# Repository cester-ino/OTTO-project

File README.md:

## OTTO-project
Hardware prototype for the OTTO Synthesizer 

Use Kicad to open the project

The main features are (for now):

 - **50 key button matrix** 
 - **4 clickable color coded encoders**
 - **1W Audio amplifier** for the internal speaker
 - **Battery management and charging** circuit for the lipo/li-ion batteries and a led battery meter  
 - **Gpio breakout** to allow to position the Raspberry rotated 90 degrees to access the USB ports and to easely use both the LCD screen and the audio card.

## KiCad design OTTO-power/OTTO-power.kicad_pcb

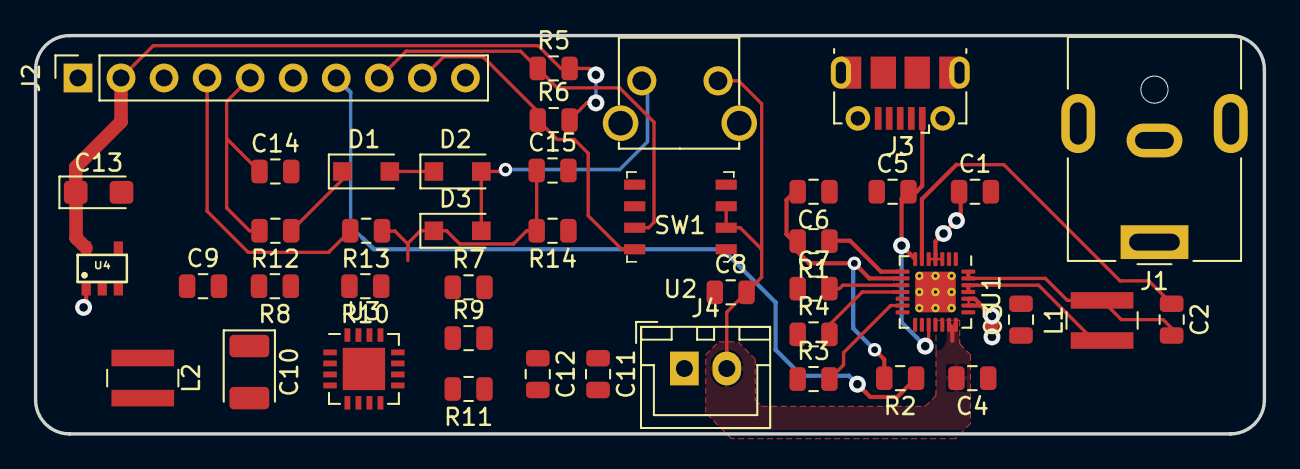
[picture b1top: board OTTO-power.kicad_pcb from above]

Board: 2 copper layers, 72.5 x 23.5 mm, 43 parts (0 on the bottom side), 27 nets.

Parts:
C1, C6, C9: 2.2uf; C_0805_2012Metric
C2: 1uf; C_0805_2012Metric
C3, C4, C11: 10uf; C_0805_2012Metric
C5: 4.7uf; C_0805_2012Metric
C7: 0.15uf; C_0805_2012Metric
C8, C12: 0.1uf; C_0805_2012Metric
C10: 100uf; CP_EIA-3528-21_Kemet-B
C13: 10uf; CP_EIA-3216-18_Kemet-A
C14, C15: 0.1uF; C_0805_2012Metric
D1, D2, D3: IN4001; D_SOD-123F
J1: Barrel_Jack; BarrelJack_CUI_PJ-063AH_Horizontal
J2: Conn_01x10; PinSocket_1x10_P2.54mm_Vertical
J3: USB_B_Micro; USB_Micro-B_Molex-105017-0001
J4: battery; JST_XH_B02B-XH-A_1x02_P2.50mm_Vertical
L1: 3.3uH; L_Wuerth_MAPI-4020
L2: 6.8uH; L_Wuerth_MAPI-4020
R1, R2, R5, R6: 100K; R_0805_2012Metric
R3: 1.2K; R_0805_2012Metric
R4: 3K; R_0805_2012Metric
R7, R10: 200K; R_0805_2012Metric
R8, R9: 1.87M; R_0805_2012Metric
R11: 340K; R_0805_2012Metric
R12, R13, R14: 10K; R_0805_2012Metric
SW1: SW_Push; SKHHLVA010
U1: MAX8903A; QFN-28-1EP_4x4mm_P0.4mm_EP2.4x2.4mm_ThermalVias
U2: MAX17048; TDFN-8-1EP
U3: TPS61090; QFN-16-1EP_4x4mm_P0.65mm_EP2.5x2.5mm
U4: XC6210; SOT25

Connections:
3V3: C13.1, J2.2, R5.2, R6.2, U4.5
5V: C9.2, C10.1, J2.3, R8.2, U3.1, U3.15, U3.16
BATT+: C4.2, C8.2, J4.2, R7.2, SW1.1, U1.20, U1.21, U2.2, U2.3
CHG_OUT: J2.7, R2.1, U1.22
DC: C1.1, J1.1, U1.3, U1.4, U1.5
DOK_OUT: J2.6, R1.1, U1.8
EN_PI: C15.1, D3.1, R7.1, R13.1, R14.2, U3.11, U4.3
GNDA: C1.2, C3.1, C4.1, C5.1, C6.1, C7.1, C8.1, C9.1, C10.2, C11.1, C12.1, C13.2, C14.2, C15.2, J1.2, J2.1, J2.10, J3.5, J4.1, R3.1, R4.1, R10.1, R11.1, R14.1, U1.1, U1.2, U1.12, U1.14, U1.15, U1.16, U2.1, U2.4, U2.6, U3.5, U3.6, U3.7, U3.10, U3.13, U3.17, U4.2
unnamed: C2.1, U1.6
unnamed: C2.2, L1.2, U1.27, U1.28
unnamed: C7.2, U1.10
unnamed: D1.1, R12.1
unnamed: D1.2, D2.1
unnamed: D2.2, D3.2, SW1.2
unnamed: L1.1, U1.25, U1.26
unnamed: L2.1, U3.3, U3.4
unnamed: R3.2, U1.13
unnamed: R4.2, U1.11
unnamed: R8.1, R10.2, U3.14
unnamed: R9.1, R11.2, U3.9
OUT_PIN: J2.4, R13.2
SCL: J2.8, R5.1, U2.7
SDA: J2.9, R6.1, U2.8
SENSE_PIN: C14.1, J2.5, R12.2
SYS: C3.2, C11.2, C12.2, L2.2, R9.2, U1.23, U1.24, U3.8, U4.1
USB: C5.2, J3.1, U1.7, U1.17
VL: C6.2, R1.2, R2.2, U1.9

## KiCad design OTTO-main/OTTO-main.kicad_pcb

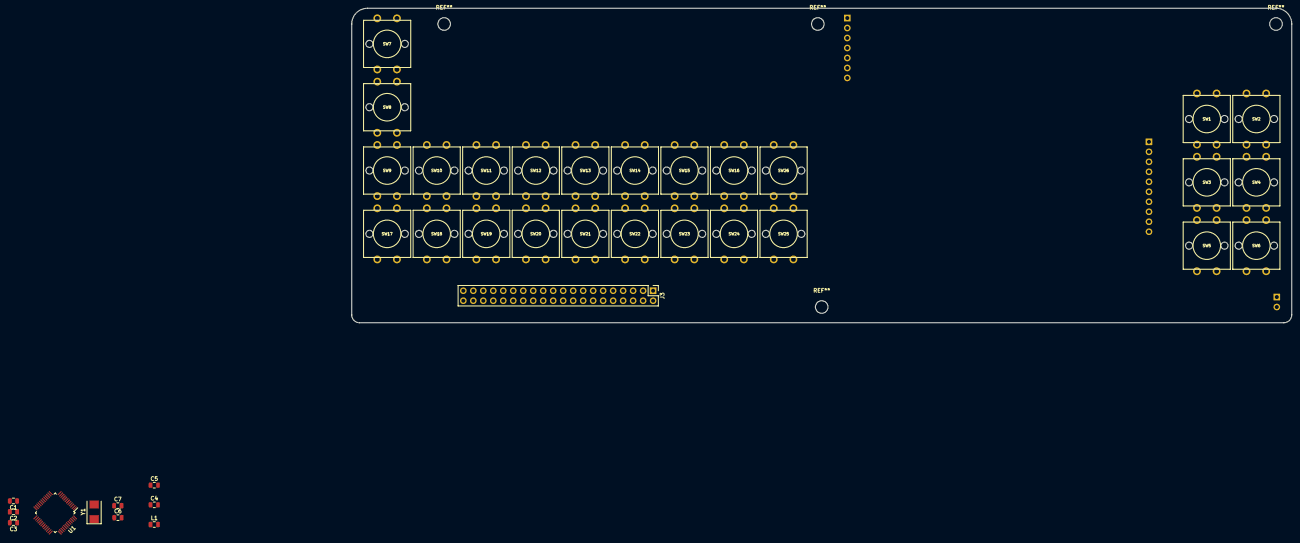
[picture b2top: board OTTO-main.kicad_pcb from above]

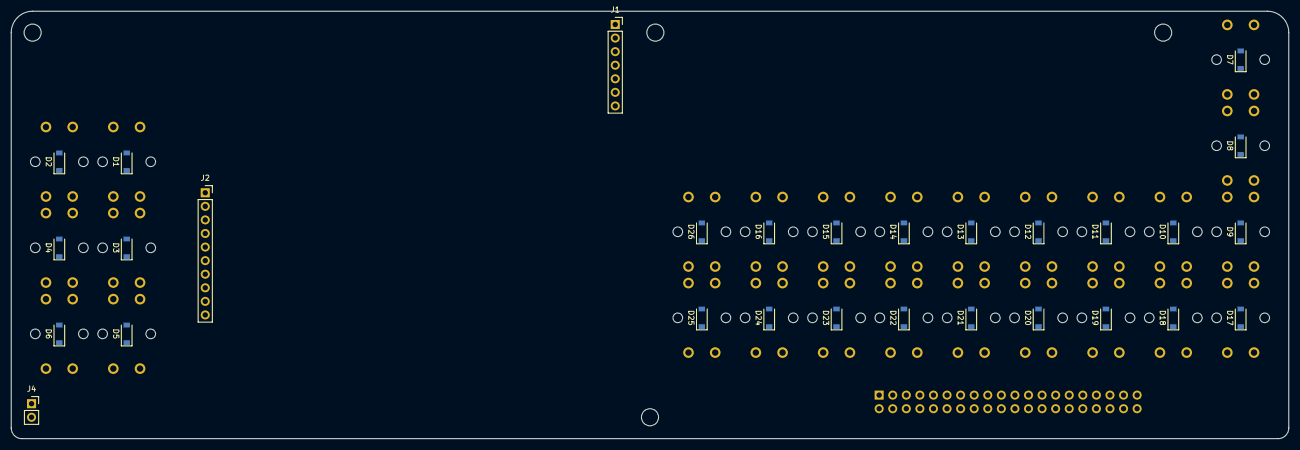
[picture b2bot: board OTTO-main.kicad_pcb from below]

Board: 2 copper layers, 239.0 x 80.0 mm, 66 parts (29 on the bottom side), 57 nets, no tracks yet.

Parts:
C1, C2, C3, C4: 1uf; C_0805_2012Metric
C5: 10nf; C_0805_2012Metric
C6, C7: 22pf; C_0805_2012Metric
D1, D2, D3, D4, D5, D6, D7, D8, D9, D10, D11, D12, D13, D14, D15, D16, D17, D18, D19, D20, D21, D22, D23, D24, D25, D26: D_ALT; D_SOD-123
J1: POWER_BOARD; PinSocket_1x07_P2.54mm_Vertical
J2: AUDIO_BOARD; PinSocket_1x10_P2.54mm_Vertical
J3: Raspberry_Pi_2_3; PinHeader_2x20_P2.54mm_Vertical
J4: MICROPHONE; PinSocket_1x02_P2.54mm_Vertical
L1: 30ohm; C_0805_2012Metric
SW1, SW2, SW3, SW4, SW5, SW6, SW7, SW8, SW9, SW10, SW11, SW12, SW13, SW14, SW15, SW16, SW17, SW18, SW19, SW20, SW21, SW22, SW23, SW24, SW25, SW26: SW_SPST; Tactile_Switch_12x12x7.3_mm
U1: STM32F103CBTx; LQFP-48_7x7mm_P0.5mm
Y1: 8mhz; Crystal_SMD_5032-2Pin_5.0x3.2mm

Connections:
5V: J1.2, J2.8
+3V3: C1.1, C2.1, C3.1, L1.2, U1.24, U1.36, U1.48
BCLK: J2.3, J3.12
COL1: D1.1, D7.1, D17.1
COL2: D2.1, D8.1, D18.1
COL3: D9.1, D19.1
COL4: D10.1, D20.1
COL5: D11.1, D21.1
COL6: D12.1, D22.1
COL7: D3.1, D13.1, D23.1
COL8: D4.1, D14.1, D24.1
COL9: D5.1, D15.1, D25.1
COL10: D6.1, D16.1, D26.1
GNDREF: C1.2, C2.2, C3.2, C4.2, C5.2, C6.2, C7.2, J2.1, J2.9, J3.6, J3.9, J3.14, J3.20, J3.25, J3.30, J3.34, J3.39, U1.44
I2S_RX: J2.4, J3.40
I2S_TX: J2.5, J3.38
LED_G: J1.6, J3.18
LED_R: J1.7, J3.22
LR_CLK: J2.2, J3.35
unnamed: C4.1, C5.1, L1.1, U1.9
unnamed: D1.2, SW1.2
unnamed: D2.2, SW2.2
unnamed: D3.2, SW3.2
unnamed: D4.2, SW4.2
unnamed: D5.2, SW5.2
unnamed: D6.2, SW6.2
unnamed: D7.2, SW7.2
unnamed: D8.2, SW8.2
unnamed: D9.2, SW9.2
unnamed: D10.2, SW10.2
unnamed: D11.2, SW11.2
unnamed: D12.2, SW12.2
unnamed: D13.2, SW13.2
unnamed: D14.2, SW14.2
unnamed: D15.2, SW15.2
unnamed: D16.2, SW16.2
unnamed: D17.2, SW17.2
unnamed: D18.2, SW18.2
unnamed: D19.2, SW19.2
unnamed: D20.2, SW20.2
unnamed: D21.2, SW21.2
unnamed: D22.2, SW22.2
unnamed: D23.2, SW23.2
unnamed: D24.2, SW24.2
unnamed: D25.2, SW25.2
unnamed: D26.2, SW26.2
OSC_IN: C6.1, U1.5, Y1.1
OSC_OUT: C7.1, U1.6, Y1.2
OUT_PIN: J1.4, J3.15
ROW1: SW1.1, SW2.1, SW3.1, SW4.1, SW5.1, SW6.1
ROW2: SW7.1, SW8.1, SW9.1, SW10.1, SW11.1, SW12.1, SW13.1, SW14.1, SW15.1, SW16.1
ROW3: SW17.1, SW18.1, SW19.1, SW20.1, SW21.1, SW22.1, SW23.1, SW24.1, SW25.1, SW26.1
SCL: J2.7, J3.5
SDA: J2.6, J3.3
SENSE_PIN: J1.5, J3.16
UART_RXD: J3.10, U1.30
UART_TXD: J3.8, U1.31

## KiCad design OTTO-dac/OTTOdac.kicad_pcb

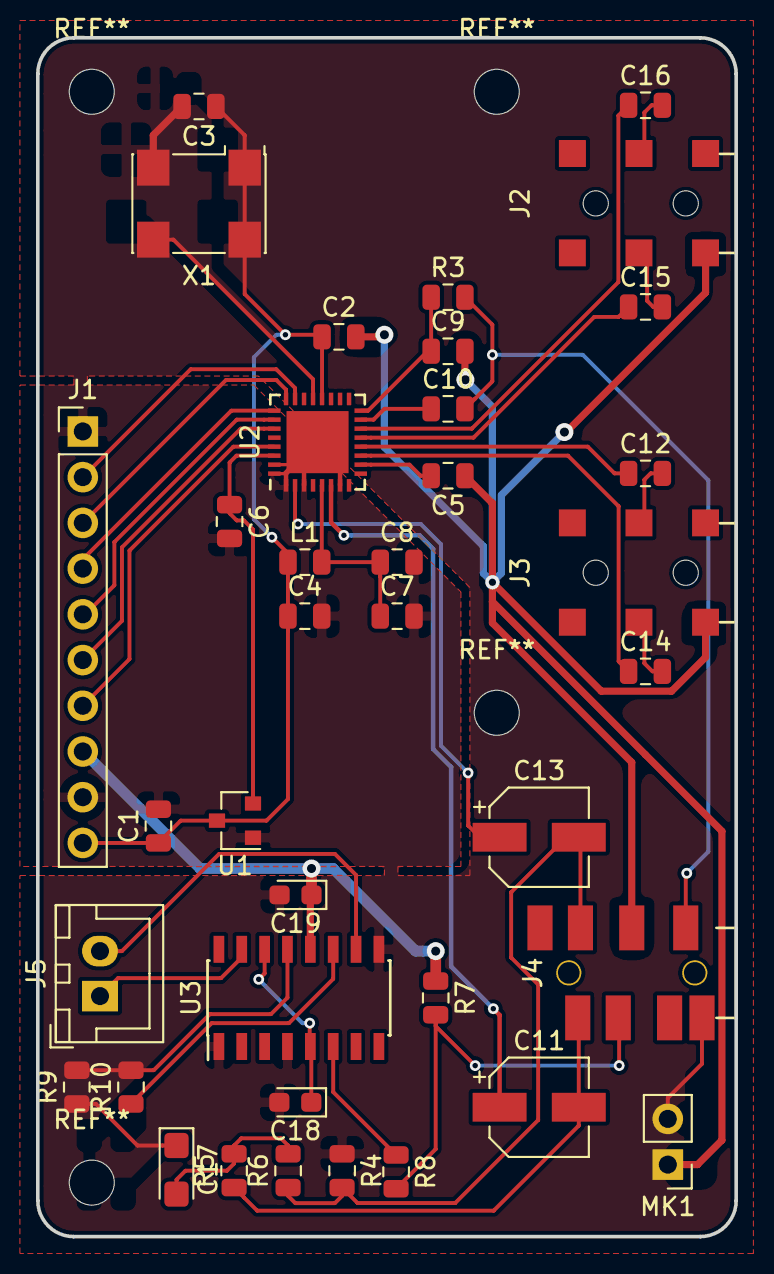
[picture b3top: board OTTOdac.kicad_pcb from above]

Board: 2 copper layers, 38.8 x 66.6 mm, 38 parts (0 on the bottom side), 39 nets.

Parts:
C1, C6, C7, C9, C12, C14, C15, C16: 2.2uf; C_0805_2012Metric
C2, C3, C4, C5, C8, C10: 0.1uf; C_0805_2012Metric
C11, C13: 220uf; CP_Elec_5x4.5
C17: 1uf; CP_EIA-3216-18_Kemet-A
C18, C19: 0.1uf; CP_EIA-2012-12_Kemet-R
J1: Conn_01x10; PinHeader_1x10_P2.54mm_Vertical
J2: Audio_IN; PJ-237-6A
J3: Audio_OUT; PJ-237-6A
J4: SJ1-42536-SMT; PJ-393-7A
J5: Speaker; JST_XH_B02B-XH-A_1x02_P2.50mm_Vertical
L1: 600; Fuse_0805_2012Metric
MK1: Microphone; PinHeader_1x02_P2.54mm_Vertical
R3: 2.2K; R_0805_2012Metric
R4, R5, R6: 1K; R_0805_2012Metric
R7, R8: 100K; R_0805_2012Metric
R9, R10: 10K; R_0805_2012Metric
U1: AMS1117-3.3; SOT-23
U2: SGTL5000; QFN-32-NXP-SGTL5000
U3: LM4860; SOIC-16_3.9x9.9mm_P1.27mm
X1: XO32; Oscillator_SMD_Abracon_ASV-4Pin_7.0x5.1mm

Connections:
+3V3: C1.1, C2.1, C3.1, C4.1, J1.10, L1.1, U1.3, U2.20, X1.1, X1.4
+5V: C19.1, J1.8, R7.1, U3.12
GNDREF: C1.2, C2.2, C3.2, C4.2, C5.1, C6.2, C7.2, C8.2, C9.2, C18.2, C19.2, J1.1, J1.9, J2.1, J3.1, J4.4, MK1.1, R4.1, U1.1, U2.1, U2.3, U2.7, U2.31, U2.32, U2.33, U3.1, U3.4, U3.9, X1.2
HPL: C11.2, J4.2, R5.1
HPR: C13.2, J4.3, R4.2, R6.1
MIC: C10.2, J4.1, R3.2
unnamed: C5.2, U2.10
unnamed: C6.1, U1.2, U2.30
unnamed: C7.1, C8.1, L1.2, U2.5
unnamed: C9.1, R3.1, U2.16
unnamed: C10.1, U2.15
unnamed: C11.1, U2.6
unnamed: C12.1, U2.12
unnamed: C12.2, J3.2
unnamed: C13.1, U2.2
unnamed: C14.1, U2.11
unnamed: C14.2, J3.3
unnamed: C15.1, U2.13
unnamed: C15.2, J2.3
unnamed: C16.1, U2.14
unnamed: C16.2, J2.2
unnamed: C17.1, R9.1
unnamed: C17.2, R5.2, R6.2
unnamed: C18.1, U3.5, U3.14
unnamed: J4.6, R7.2, R8.2
unnamed: J4.8, MK1.2
unnamed: J5.1, U3.15
unnamed: J5.2, U3.10
unnamed: R8.1, U3.6
unnamed: R10.1, U3.11
unnamed: R9.2, R10.2, U3.13
unnamed: U2.21, X1.3
unnamed: U3.2, U3.3
PIN3: J1.6, U2.27
PIN5: J1.7, U2.29
PIN12: J1.3, U2.24
PIN35: J1.2, U2.23
PIN38: J1.5, U2.26
PIN40: J1.4, U2.25

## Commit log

2018-09-11 first upload
2018-09-13 cleaned schematics
2018-09-14 new board, still needs gnd to be routed
2018-09-14 new board, need to route the DC connector (and make a protection circuit between it and the usb)
2018-09-14 added a dxf file to help align the boards and connectors
2018-09-14 routed ground and added mounting holes
2018-09-15 started working on the mainboard
2018-09-16 some progress on the main board design
2018-09-17 mainboard
2018-09-19 new powerboard circuit
2018-09-20 some advancement on the power board layout
2018-09-24 some rework on the routing
2018-09-24 solved some issues with the libraries
